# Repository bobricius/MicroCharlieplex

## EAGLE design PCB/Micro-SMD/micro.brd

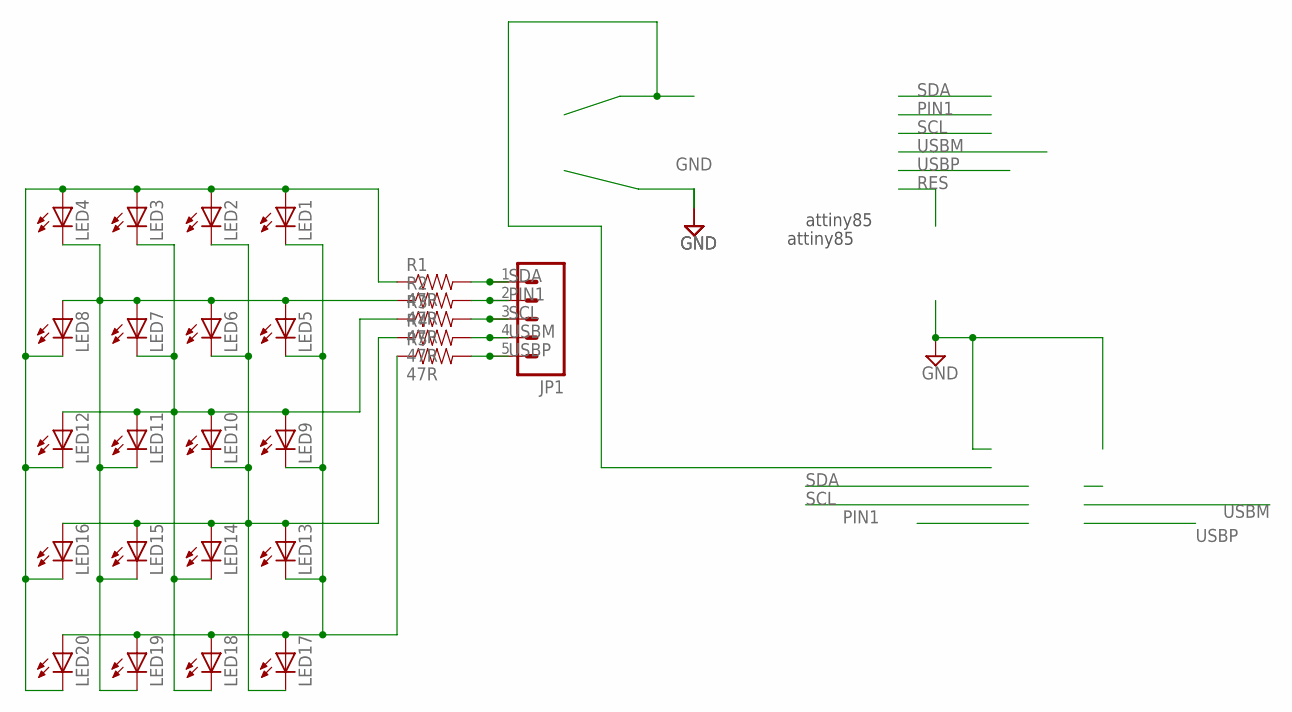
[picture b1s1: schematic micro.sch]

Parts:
JP1: M05PTH; 1X05
LED1, LED2, LED3, LED4, LED5, LED6, LED7, LED8, LED9, LED10, LED11, LED12, LED13, LED14, LED15, LED16, LED17, LED18, LED19, LED20: LEDCHIPLED_0603; CHIPLED_0603
R1, R2, R3, R4, R5: 47R; 0603-RES

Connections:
unnamed: LED1.A, LED2.A, LED3.A, LED4.A, LED8.C, LED12.C, LED16.C, LED20.C, R1.1
unnamed: LED4.C, LED5.A, LED6.A, LED7.A, LED8.A, LED11.C, LED15.C, LED19.C, R2.1
unnamed: LED3.C, LED7.C, LED9.A, LED10.A, LED11.A, LED12.A, LED14.C, LED18.C, R3.1
unnamed: LED2.C, LED6.C, LED10.C, LED13.A, LED14.A, LED15.A, LED16.A, LED17.C, R4.1
unnamed: LED1.C, LED5.C, LED9.C, LED13.C, LED17.A, LED18.A, LED19.A, LED20.A, R5.1
PIN1: JP1.2, R2.2
SCL: JP1.3, R3.2
SDA: JP1.1, R1.2
USBM: JP1.4, R4.2
USBP: JP1.5, R5.2

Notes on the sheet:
attiny85

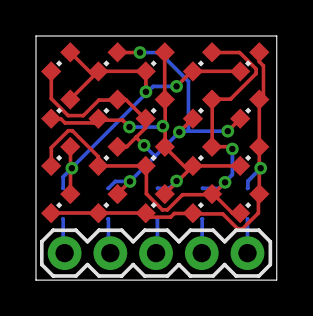
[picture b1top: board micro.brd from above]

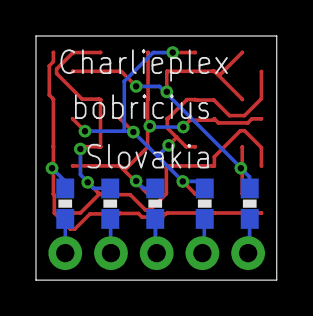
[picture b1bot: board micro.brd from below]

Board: 2 copper layers, 13.4 x 13.6 mm, 26 parts (5 on the bottom side), 10 nets.

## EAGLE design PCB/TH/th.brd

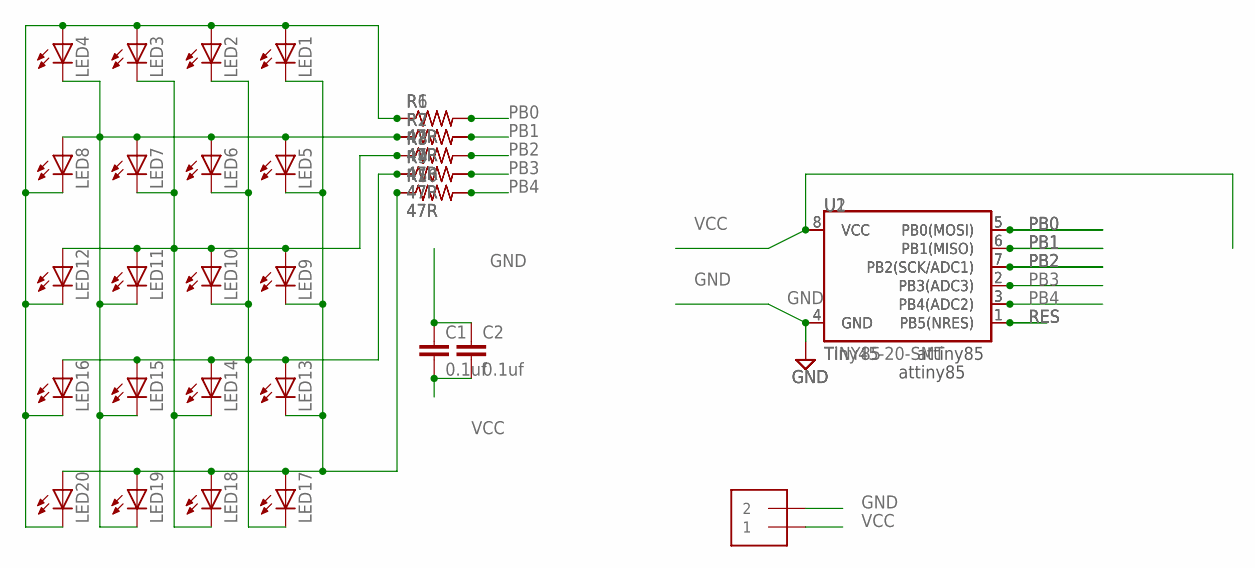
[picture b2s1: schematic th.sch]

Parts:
C1: 0.1uf; 0603-CAP
C2: 0.1uf; CAP-PTH-SMALL-KIT
J1: 1X2-3.5MM
LED1, LED2, LED3, LED4, LED5, LED6, LED7, LED8, LED9, LED10, LED11, LED12, LED13, LED14, LED15, LED16, LED17, LED18, LED19, LED20: LED3MM
R1, R2, R3, R4, R5: 47R; AXIAL-0.3
R6, R7, R8, R9, R10: 47R; 0603-RES
U1: TINY85; DIP08
U2: Tiny45-20-SMT; SO08-EIAJ

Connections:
GND: C1.1, C2.1, J1.2, U1.4 (GND), U2.4 (GND)
unnamed: LED1.A, LED2.A, LED3.A, LED4.A, LED8.K (C), LED12.K (C), LED16.K (C), LED20.K (C), R1.P$1 (1), R6.1
unnamed: LED4.K (C), LED5.A, LED6.A, LED7.A, LED8.A, LED11.K (C), LED15.K (C), LED19.K (C), R2.P$1 (1), R7.1
unnamed: LED3.K (C), LED7.K (C), LED9.A, LED10.A, LED11.A, LED12.A, LED14.K (C), LED18.K (C), R3.P$1 (1), R8.1
unnamed: LED2.K (C), LED6.K (C), LED10.K (C), LED13.A, LED14.A, LED15.A, LED16.A, LED17.K (C), R4.P$1 (1), R9.1
unnamed: LED1.K (C), LED5.K (C), LED9.K (C), LED13.K (C), LED17.A, LED18.A, LED19.A, LED20.A, R5.P$1 (1), R10.1
PB0: R1.P$2 (2), R6.2, U1.5 (PB0(MOSI)), U2.5 (PB0(MOSI))
PB1: R2.P$2 (2), R7.2, U1.6 (PB1(MISO)), U2.6 (PB1(MISO))
PB2: R3.P$2 (2), R8.2, U1.7 (PB2(SCK/ADC1)), U2.7 (PB2(SCK/ADC1))
PB3: R4.P$2 (2), R9.2, U1.2 (PB3(ADC3)), U2.2 (PB3(ADC3))
PB4: R5.P$2 (2), R10.2, U1.3 (PB4(ADC2)), U2.3 (PB4(ADC2))
RES: U1.1 (PB5(NRES)), U2.1 (PB5(NRES))
VCC: C1.2, C2.2, J1.1, U1.8 (VCC), U2.8 (VCC)

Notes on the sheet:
attiny85

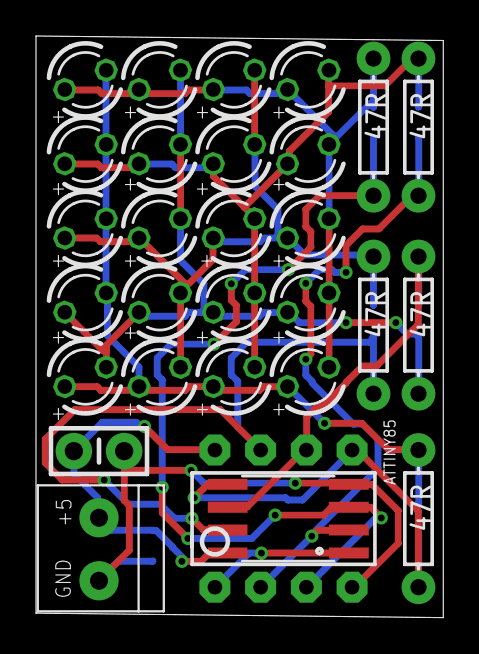
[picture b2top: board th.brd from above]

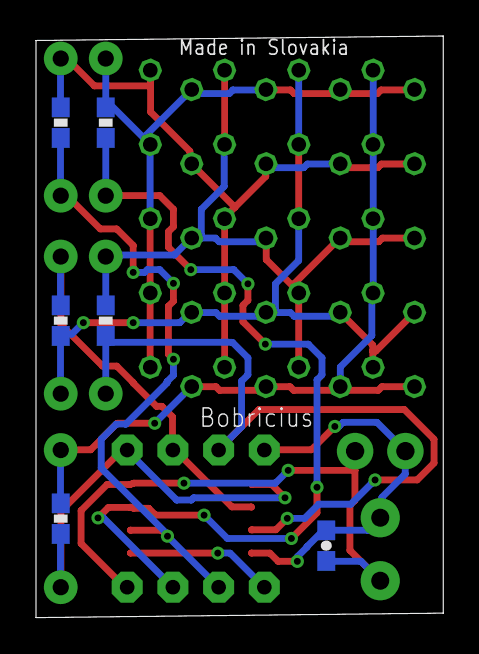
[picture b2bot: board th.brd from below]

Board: 2 copper layers, 22.6 x 32.3 mm, 35 parts (6 on the bottom side), 13 nets.

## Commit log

2014-11-12 :lollipop: Added .gitattributes & .gitignore files
2014-11-12 first upload

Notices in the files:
parts and their libraries:
SparkFun: Licensing: CC v3.0 Share-Alike You are welcome to use this library for commercial purposes.
